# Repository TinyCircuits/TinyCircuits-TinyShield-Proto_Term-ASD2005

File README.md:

# TinyCircuits TinyShield Proto Terminal Block Board
# ASD2005 Rev2

The design files are located under design_files/ for the TinyCircuits ASD2005 Rev 2 PCB.  This is a TinyShield board (32mm x 29mm) that has the shield signals brought out to terminal blocks.

Format is in Cadsoft Eagle format - Eagle version 6.2 was used for the original design.

For more infomation on this, check out the product page at TinyCircuits.com:  https://tinycircuits.com/collections/proto-boards/products/proto-terminal-blocks-tinyshield?variant=14984805511

# License:

Design by TinyCircuits.
All design files are released under the Creative Commons Attribution Share-Alike 3.0 License, see the following link for details: http://creativecommons.org/licenses/by-sa/3.0

All text above must be included in any redistribution or derived design

This project uses designs and concepts developed as part of the Arduino project and the LilyPad project.  The TinyCircuits design files themselves (schematics, PCB and libraries) are not directly derived from these works' design files and have been created new, however the concepts and basic architecture behind the TinyDuino and TinyLily products are derived and we thank the hard work of the organizations below for their contributions to open-source hardware:
  
Original Arduino Uno Design by Team Arduino

LilyPad Arduino Design by Leah Buechley and Sparkfun Electronics

Please support the open-source hardware community

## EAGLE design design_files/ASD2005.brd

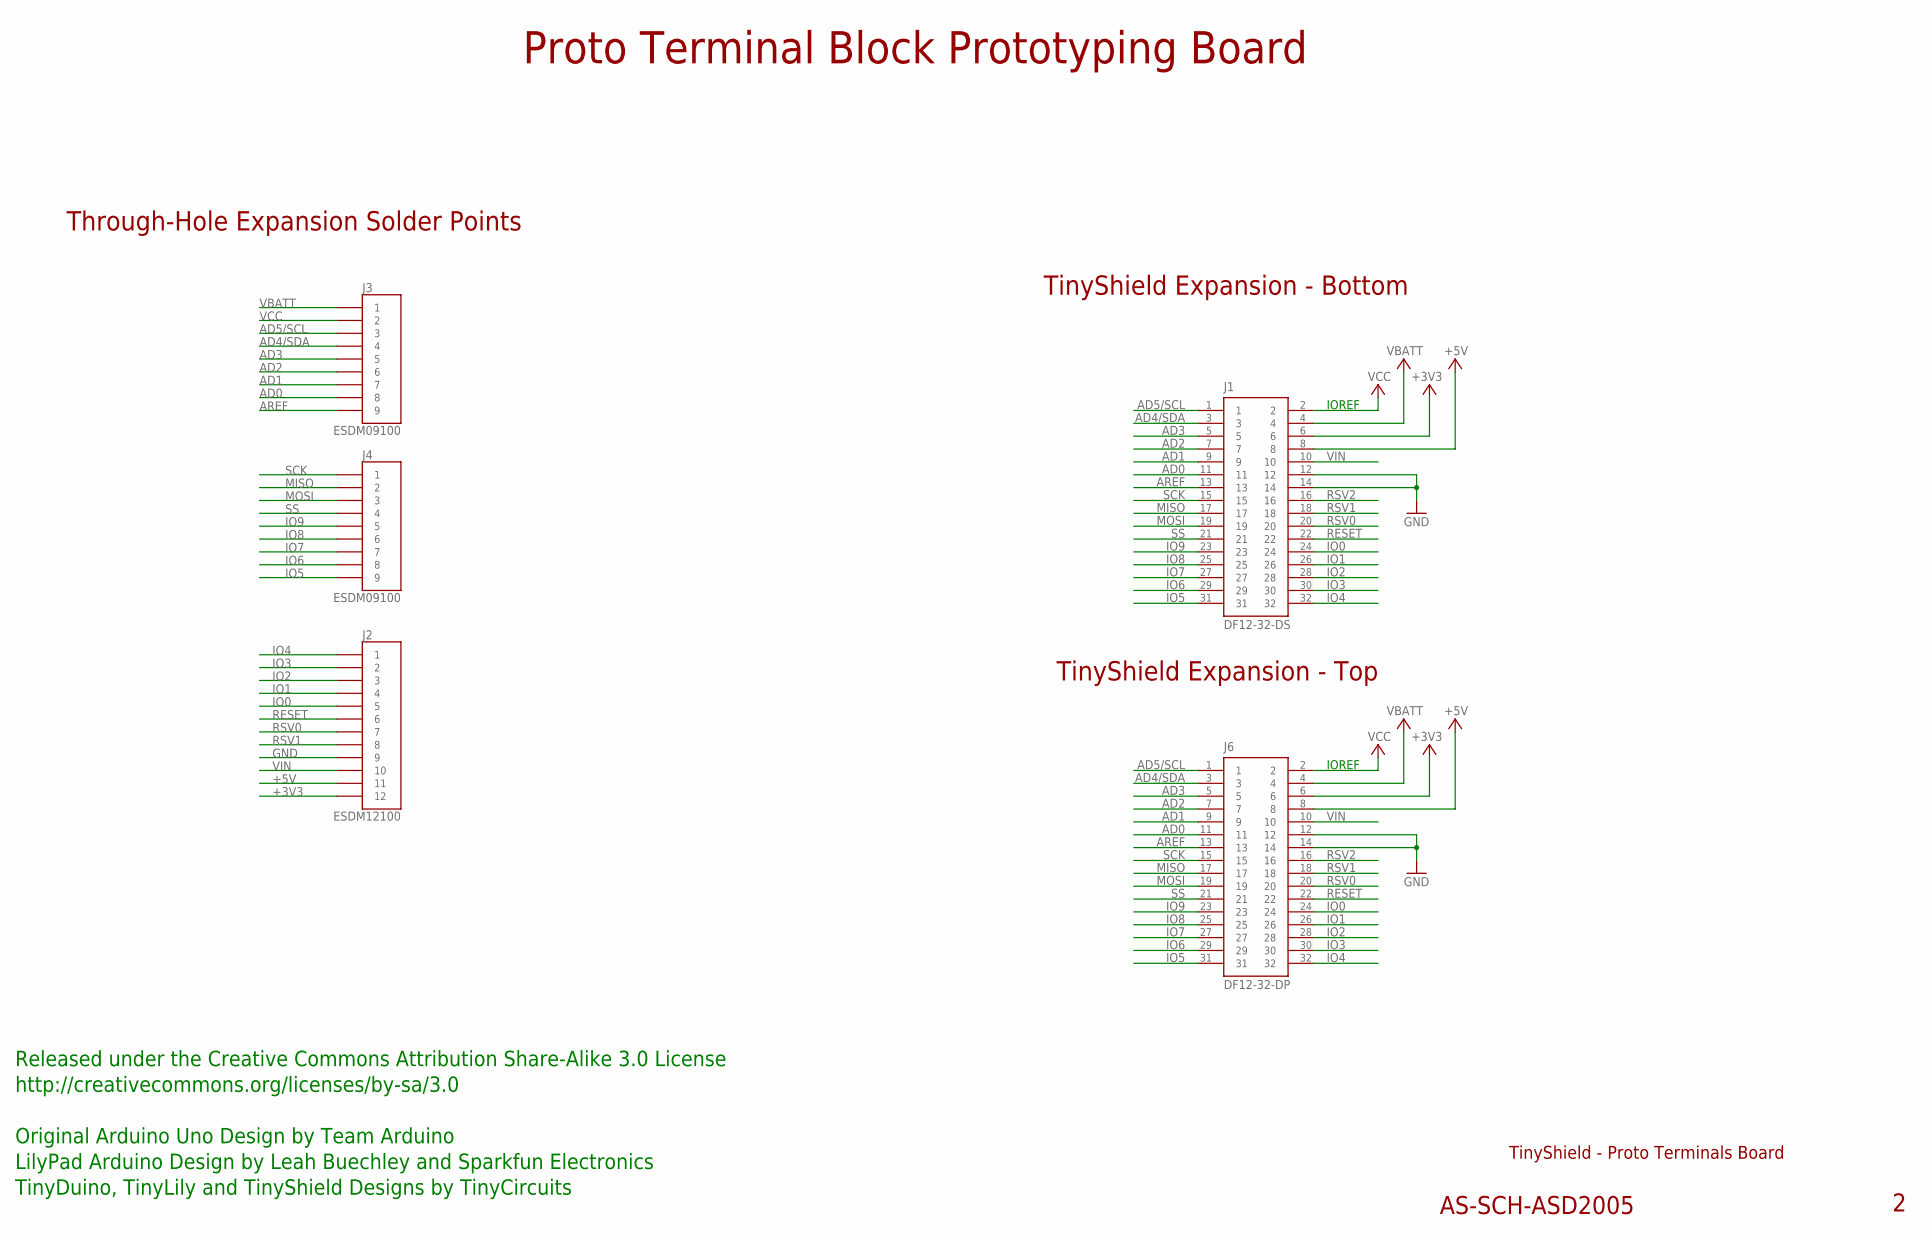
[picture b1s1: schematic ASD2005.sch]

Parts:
J1: DF12-32-DS; PARTNO AS-ITM-00012
J2: ESDM12100; 12POS_2.54MM_TERMBLOCK
J3, J4: ESDM09100; 9POS_2.54MM_TERMBLOCK
J6: DF12-32-DP; PARTNO AS-ITM-00015

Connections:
+3V3: J1.6, J2.P$13 (12), J6.6
+5V: J1.8, J2.P$12 (11), J6.8
AD0: J1.11, J3.P$8 (8), J6.11
AD1: J1.9, J3.P$7 (7), J6.9
AD2: J1.7, J3.P$6 (6), J6.7
AD3: J1.5, J3.P$5 (5), J6.5
AD4/SDA: J1.3, J3.P$4 (4), J6.3
AD5/SCL: J1.1, J3.P$3 (3), J6.1
AREF: J1.13, J3.P$9 (9), J6.13
GND: J1.12, J1.14, J2.P$9 (9), J6.12, J6.14
IO0: J1.24, J2.P$5 (5), J6.24
IO1: J1.26, J2.P$4 (4), J6.26
IO2: J1.28, J2.P$3 (3), J6.28
IO3: J1.30, J2.P$2 (2), J6.30
IO4: J1.32, J2.P$1 (1), J6.32
IO5: J1.31, J4.P$9 (9), J6.31
IO6: J1.29, J4.P$8 (8), J6.29
IO7: J1.27, J4.P$7 (7), J6.27
IO8: J1.25, J4.P$6 (6), J6.25
IO9: J1.23, J4.P$5 (5), J6.23
MISO: J1.17, J4.P$2 (2), J6.17
MOSI: J1.19, J4.P$3 (3), J6.19
RESET: J1.22, J2.P$6 (6), J6.22
RSV0: J1.20, J2.P$7 (7), J6.20
RSV1: J1.18, J2.P$8 (8), J6.18
RSV2: J1.16, J6.16
SCK: J1.15, J4.P$1 (1), J6.15
SS: J1.21, J4.P$4 (4), J6.21
VBATT: J1.4, J3.P$1 (1), J6.4
VCC: J1.2, J3.P$2 (2), J6.2
VIN: J1.10, J2.P$10 (10), J6.10

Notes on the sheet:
TinyShield Expansion - Bottom
TinyShield - Proto Terminals Board
AS-SCH-ASD2005
IOREF
Released under the Creative Commons Attribution Share-Alike 3.0 License
http://creativecommons.org/licenses/by-sa/3.0
LilyPad Arduino Design by Leah Buechley and Sparkfun Electronics
TinyDuino, TinyLily and TinyShield Designs by TinyCircuits
Through-Hole Expansion Solder Points
Original Arduino Uno Design by Team Arduino
Proto Terminal Block Prototyping Board
TinyShield Expansion - Top

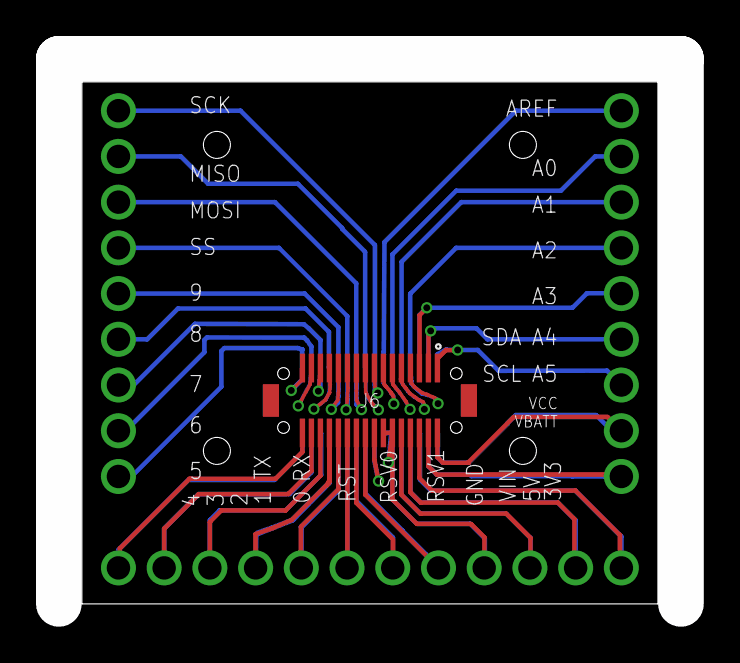
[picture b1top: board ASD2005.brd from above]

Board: 2 copper layers, 34.6 x 30.3 mm, 6 parts (1 on the bottom side), 31 nets.

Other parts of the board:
U$1: DOCFIELD-TINYCIRCUITS-PCB

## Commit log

2019-01-04 updates format
2020-07-28 Add CAD data
2020-08-14 Update CAD drawing
